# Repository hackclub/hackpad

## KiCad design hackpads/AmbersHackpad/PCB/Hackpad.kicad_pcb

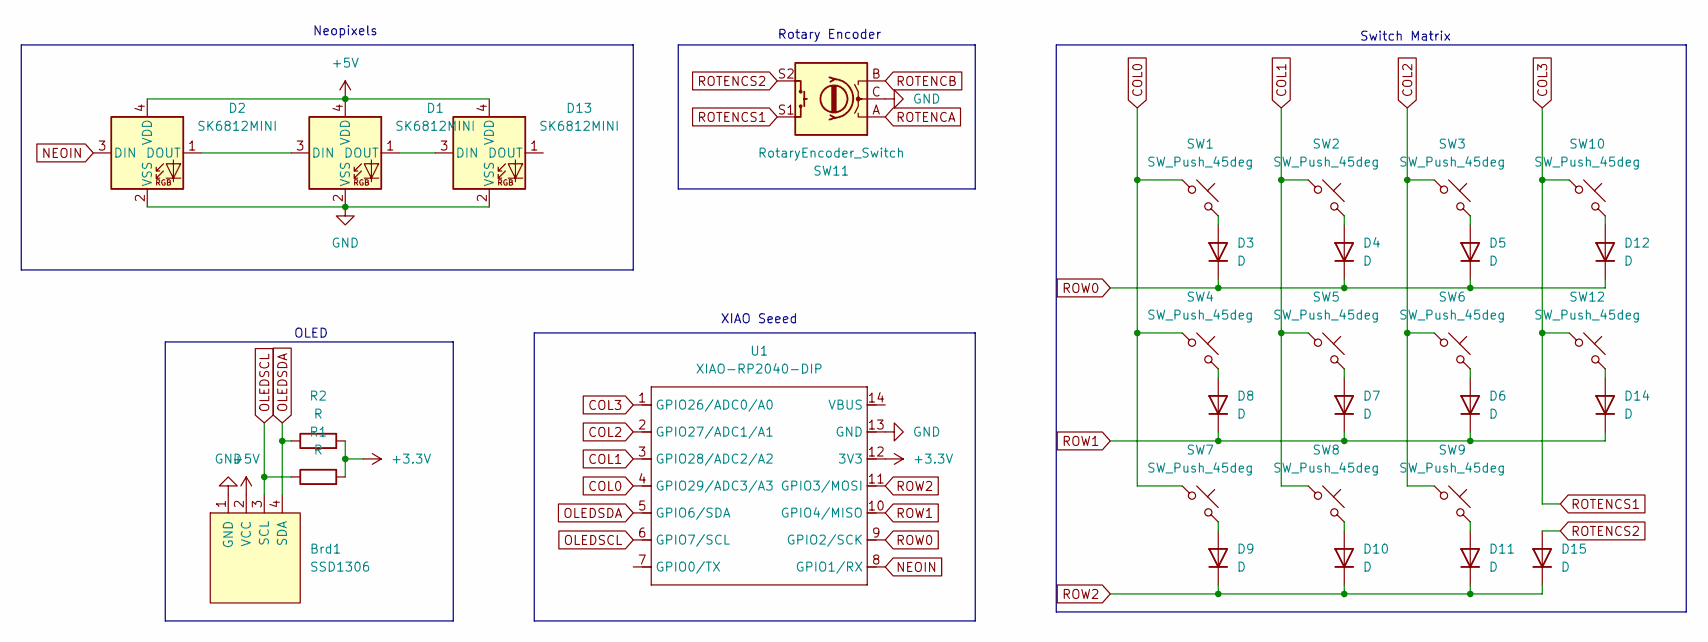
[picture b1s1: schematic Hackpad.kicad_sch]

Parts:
Brd1: SSD1306; 128x64OLED
D1, D2, D13: SK6812MINI; LED_SK6812MINI_PLCC4_3.5x3.5mm_P1.75mm_3D
D3, D4, D5, D6, D7, D8, D9, D10, D11, D12, D14, D15: D; D_DO-35_SOD27_P7.62mm_Horizontal
R1, R2: R; R_Axial_DIN0204_L3.6mm_D1.6mm_P7.62mm_Horizontal
SW1, SW2, SW3, SW4, SW5, SW6, SW7, SW8, SW9, SW10, SW12: SW_Push_45deg; SW_Cherry_MX_1.00u_PCB_3D
SW11: RotaryEncoder_Switch; RotaryEncoder_Alps_EC11E-Switch_Vertical_H20mm_CircularMoun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
U1: XIAO-RP2040-DIP; XIAO-RP2040-DIP-3D

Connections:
+3.3V: R1.2, R2.2, U1.12 (3V3)
+5V: Brd1.2 (VCC), D1.4 (VDD), D2.4 (VDD), D13.4 (VDD)
COL0: SW1.1, SW4.1, SW7.1, U1.4 (GPIO29/ADC3/A3)
COL1: SW2.1, SW5.1, SW8.1, U1.3 (GPIO28/ADC2/A2)
COL2: SW3.1, SW6.1, SW9.1, U1.2 (GPIO27/ADC1/A1)
COL3: SW10.1, SW11.S1, SW12.1, U1.1 (GPIO26/ADC0/A0)
GND: Brd1.1 (GND), D1.2 (VSS), D2.2 (VSS), D13.2 (VSS), SW11.C, U1.13 (GND)
NEOIN: D2.3 (DIN), U1.8 (GPIO1/RX)
unnamed: D1.3 (DIN), D2.1 (DOUT)
unnamed: D1.1 (DOUT), D13.3 (DIN)
unnamed: D3.2 (A), SW1.2
unnamed: D4.2 (A), SW2.2
unnamed: D5.2 (A), SW3.2
unnamed: D6.2 (A), SW6.2
unnamed: D7.2 (A), SW5.2
unnamed: D8.2 (A), SW4.2
unnamed: D9.2 (A), SW7.2
unnamed: D10.2 (A), SW8.2
unnamed: D11.2 (A), SW9.2
unnamed: D12.2 (A), SW10.2
unnamed: D14.2 (A), SW12.2
OLEDSCL: Brd1.3 (SCL), R1.1, U1.6 (GPIO7/SCL)
OLEDSDA: Brd1.4 (SDA), R2.1, U1.5 (GPIO6/SDA)
ROTENCA: SW11.A
ROTENCB: SW11.B
ROTENCS2: D15.2 (A), SW11.S2
ROW0: D3.1 (K), D4.1 (K), D5.1 (K), D12.1 (K), U1.9 (GPIO2/SCK)
ROW1: D6.1 (K), D7.1 (K), D8.1 (K), D14.1 (K), U1.10 (GPIO4/MISO)
ROW2: D9.1 (K), D10.1 (K), D11.1 (K), D15.1 (K), U1.11 (GPIO3/MOSI)

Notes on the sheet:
XIAO Seeed
Neopixels
Rotary Encoder
OLED
Switch Matrix

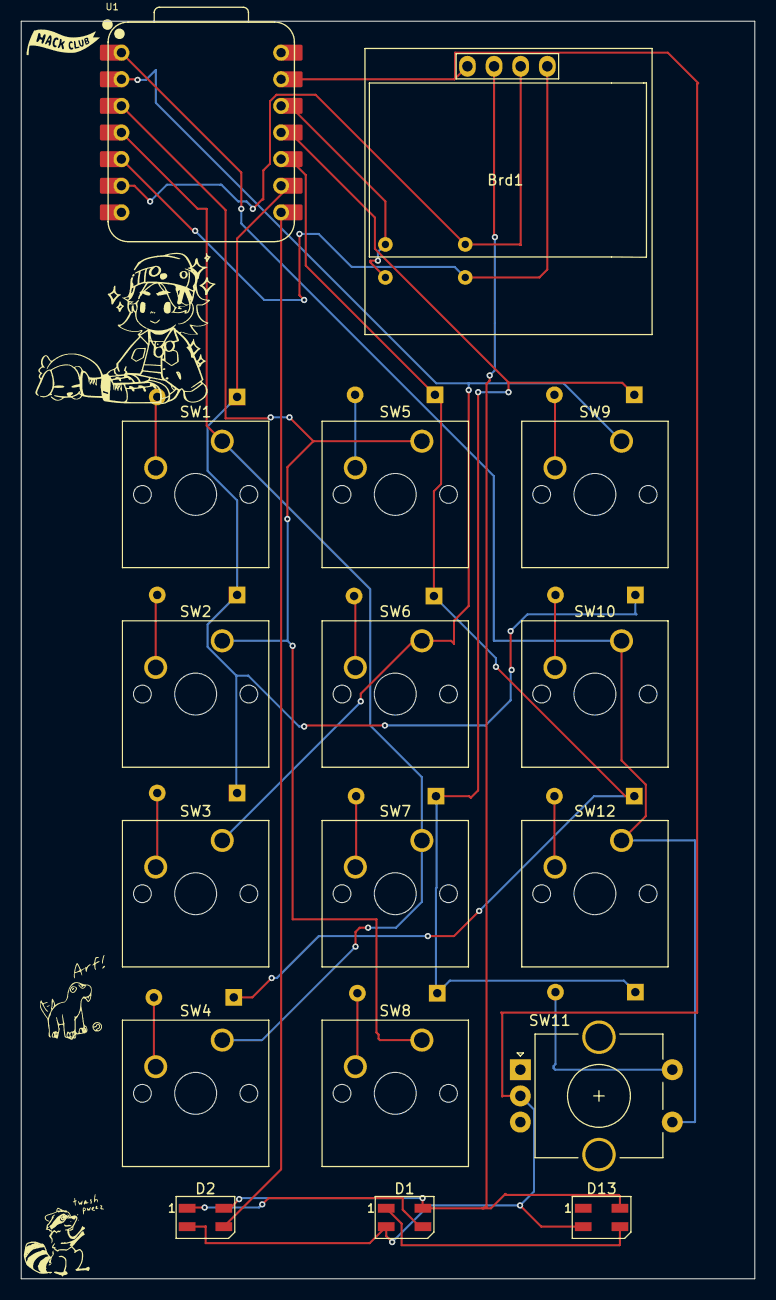
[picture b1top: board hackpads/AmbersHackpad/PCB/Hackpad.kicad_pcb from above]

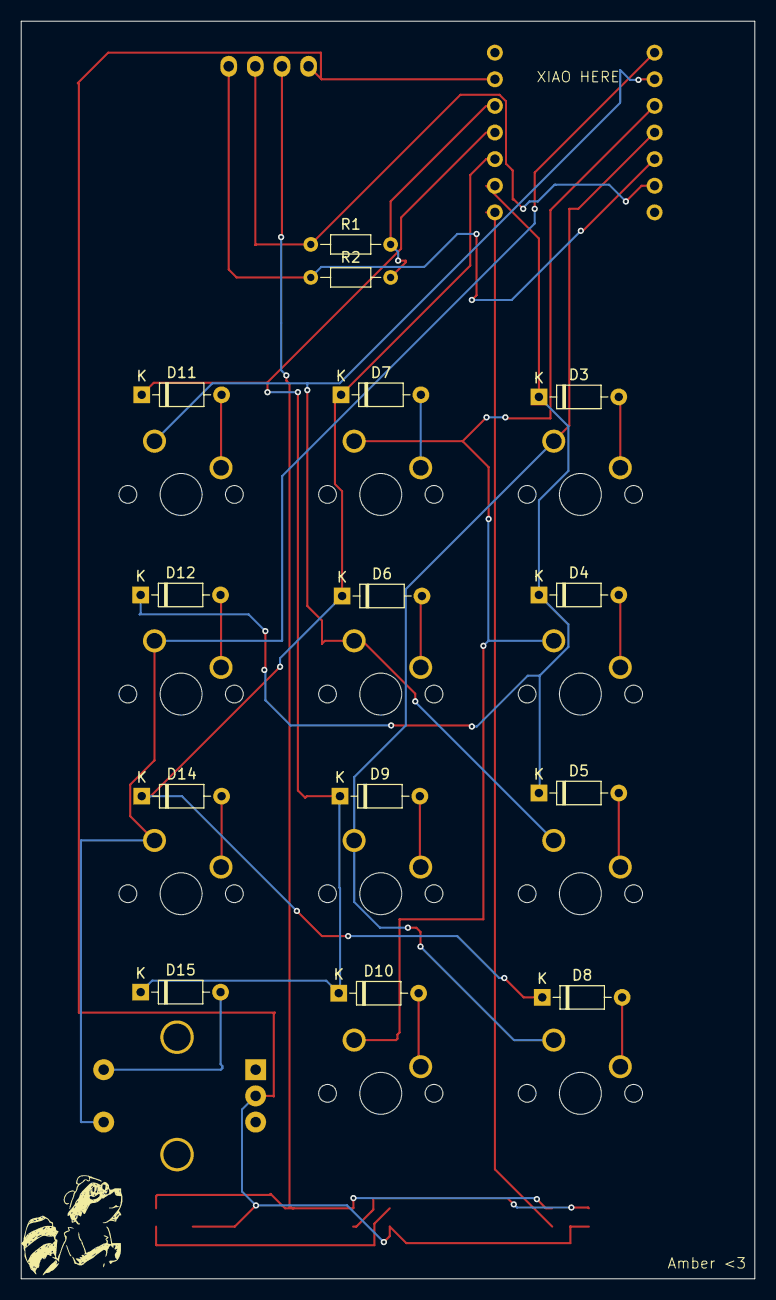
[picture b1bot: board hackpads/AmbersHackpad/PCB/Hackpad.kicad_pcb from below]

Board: 2 copper layers, 70.0 x 120.0 mm, 31 parts (14 on the bottom side), 27 nets.

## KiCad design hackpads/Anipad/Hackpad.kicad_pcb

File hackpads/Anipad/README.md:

# The Anipad

## Overview

Hey! This is Anicetus, and here is my Hackpad, a macropad project from https://hackclub.com. It uses a Seeed Studio XIAO RP2040 with a custom-made case, PCB, and QMK firmware.
It has 11 buttons (not including the rotary encoder) aligned in a 4x3 matrix. The Anipad's primary use is to control my 3D printer without access to a phone or computer. It'll plug into my Raspberry Pi which controls the printer and send commands to print files, move the axes, etc.
The Anipad is equipped with a 0.91" OLED screen and a rotary encoder.

## About the Anipad

I can shamelessly say that I copied @grimsteel a lot on Slack. He was a big help to getting this thing rolling. However, most of the PCB and all of the case is my own design. On the back of the case is a Penrose Triangle, commonly known as the Impossible Triangle. I have a semi-obssession with it, and it only seemed right to include it.
The name "Anipad" comes from my name, Anicetus, which means "Unconquerable" in Latin, a language I'm proud to say I can speak ~~decently well~~ OK I guess. Autem, sum non bonus in conspectu populi.
<br/>***ANYWAYS***, I love coding, making, and hacking, and despite arriving with less than 10 days left in the Hackpad project, I feel I did decently well. And, of course, I needed to add its name in the front.
<br/>

<br/>
<br/>
~ Anicetus
<br/>
<sub>Holy cow was designing the case hard<sub>

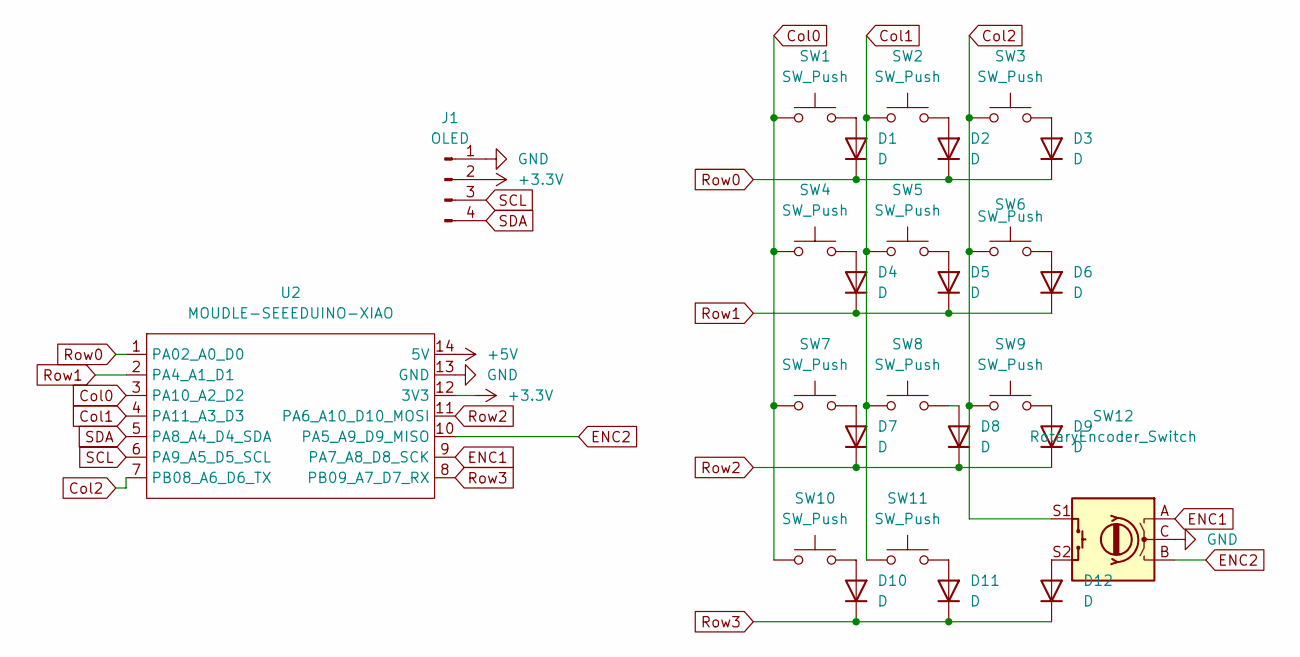
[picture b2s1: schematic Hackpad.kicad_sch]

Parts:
D1, D2, D3, D4, D5, D6, D7, D8, D9, D10, D11, D12: D; D_DO-35_SOD27_P7.62mm_Horizontal
J1: OLED; SSD1306-0.91-OLED-4pin-128x32
SW1, SW2, SW3, SW4, SW5, SW6, SW7, SW8, SW9, SW10, SW11: SW_Push; SW_Cherry_MX_1.00u_PCB
SW12: RotaryEncoder_Switch; RotaryEncoder_Alps_EC11E-Switch_Vertical_H20mm
U2: MOUDLE-SEEEDUINO-XIAO; XIAO-Generic-Thruhole-14P-2.54-21X17.8MM

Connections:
+3.3V: J1.2, U2.12 (3V3)
+5V: U2.14 (5V)
Col0: SW1.1, SW4.1, SW7.1, SW10.1, U2.3 (PA10_A2_D2)
Col1: SW2.1, SW5.1, SW8.1, SW11.1, U2.4 (PA11_A3_D3)
Col2: SW3.1, SW6.1, SW9.1, SW12.S1, U2.7 (PB08_A6_D6_TX)
ENC1: SW12.A, U2.9 (PA7_A8_D8_SCK)
ENC2: SW12.B, U2.10 (PA5_A9_D9_MISO)
GND: J1.1, SW12.C, U2.13 (GND)
unnamed: D1.2 (A), SW1.2
unnamed: D2.2 (A), SW2.2
unnamed: D3.2 (A), SW3.2
unnamed: D4.2 (A), SW4.2
unnamed: D5.2 (A), SW5.2
unnamed: D6.2 (A), SW6.2
unnamed: D7.2 (A), SW7.2
unnamed: D8.2 (A), SW8.2
unnamed: D9.2 (A), SW9.2
unnamed: D10.2 (A), SW10.2
unnamed: D11.2 (A), SW11.2
unnamed: D12.2 (A), SW12.S2
Row0: D1.1 (K), D2.1 (K), D3.1 (K), U2.1 (PA02_A0_D0)
Row1: D4.1 (K), D5.1 (K), D6.1 (K), U2.2 (PA4_A1_D1)
Row2: D7.1 (K), D8.1 (K), D9.1 (K), U2.11 (PA6_A10_D10_MOSI)
Row3: D10.1 (K), D11.1 (K), D12.1 (K), U2.8 (PB09_A7_D7_RX)
SCL: J1.3, U2.6 (PA9_A5_D5_SCL)
SDA: J1.4, U2.5 (PA8_A4_D4_SDA)

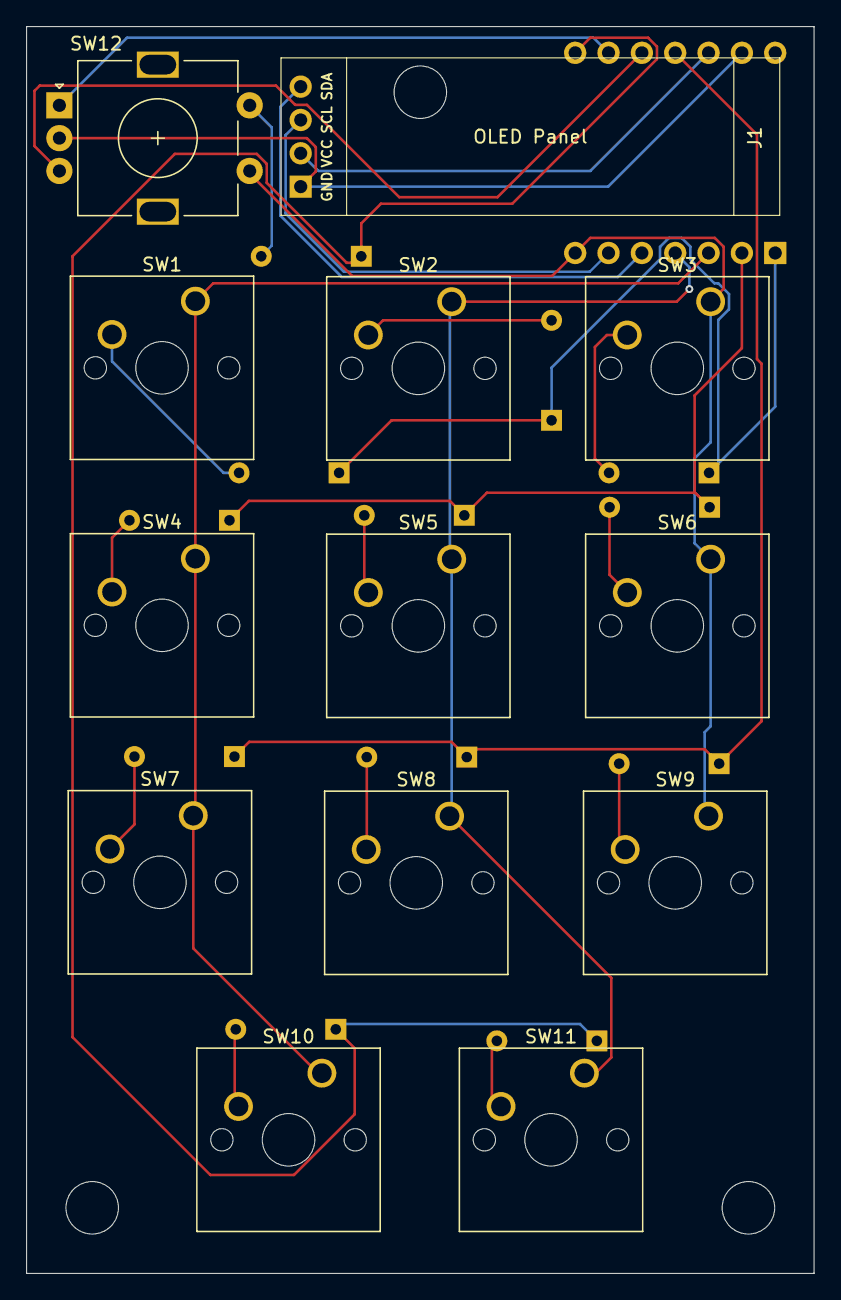
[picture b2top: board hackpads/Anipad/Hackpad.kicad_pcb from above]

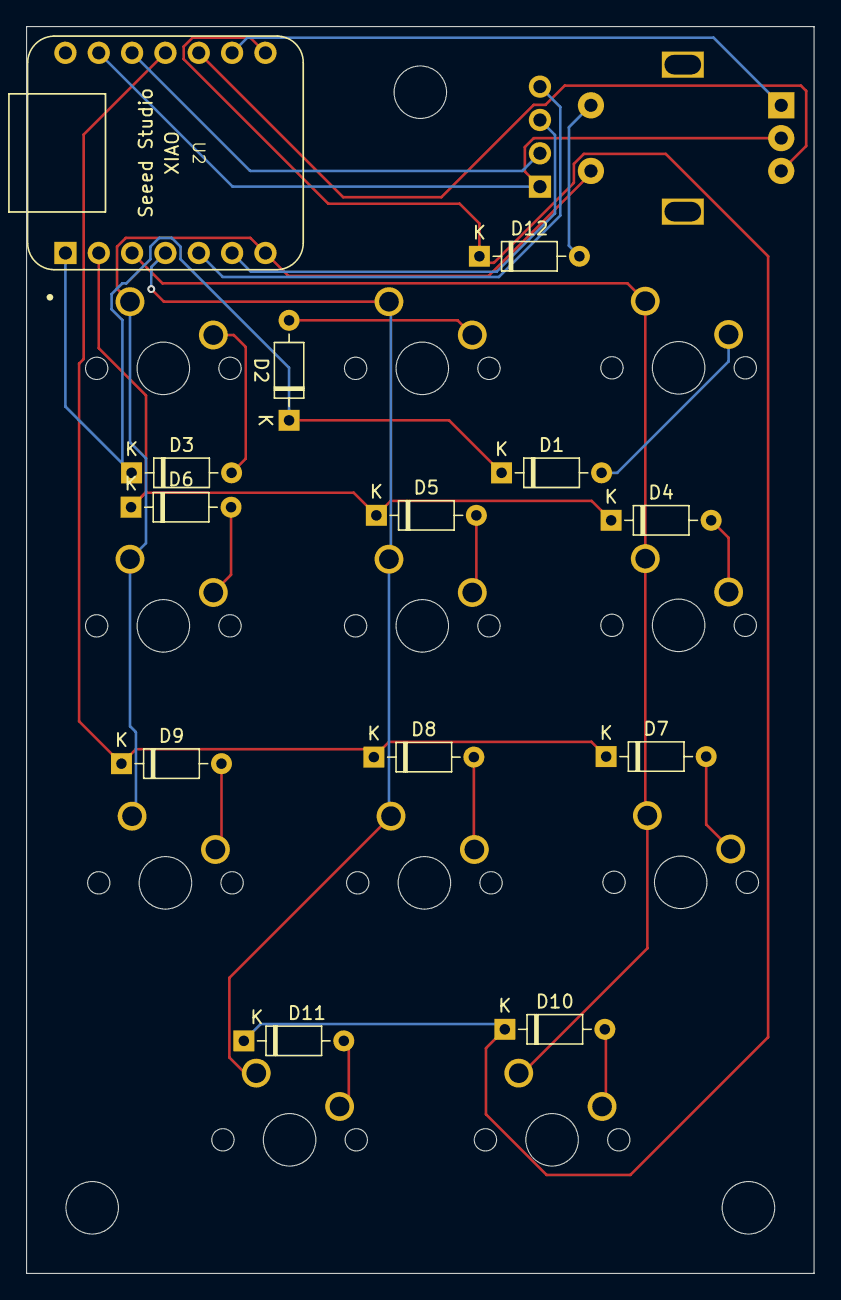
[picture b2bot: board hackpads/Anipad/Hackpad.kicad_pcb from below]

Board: 2 copper layers, 60.0 x 95.0 mm, 26 parts (13 on the bottom side), 25 nets.

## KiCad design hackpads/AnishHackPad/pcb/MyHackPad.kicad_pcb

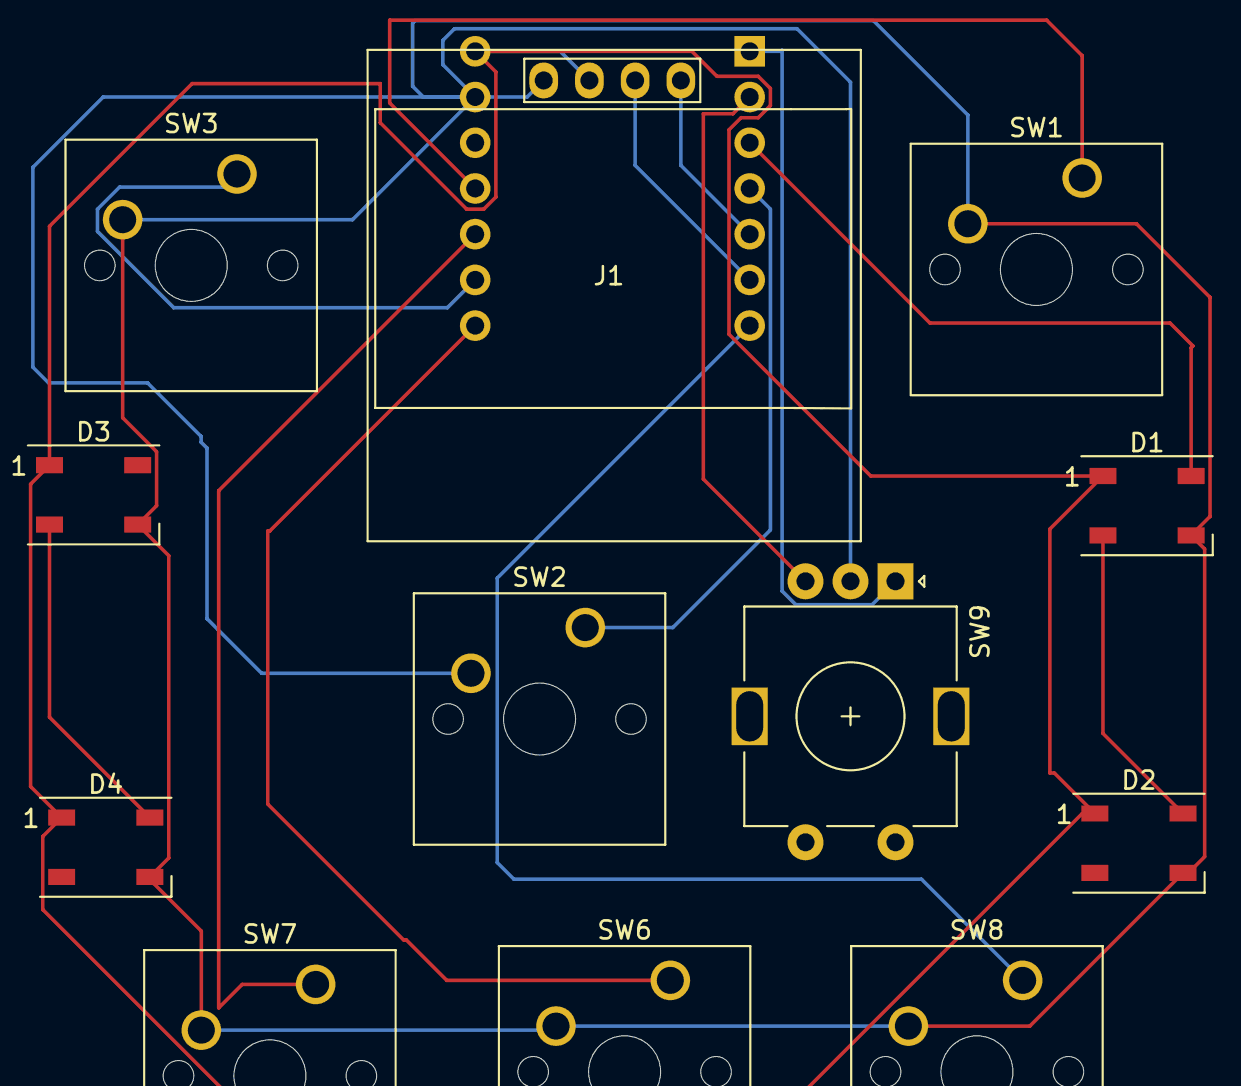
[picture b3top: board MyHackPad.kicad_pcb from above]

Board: 2 copper layers, 13 parts (1 on the bottom side), 16 nets.

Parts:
D1, D2, D3, D4: WS2812B; LED_WS2812B_PLCC4_5.0x5.0mm_P3.2mm
J1: OLED-128x64; 128x64OLED
SW1, SW2, SW3, SW6, SW7, SW8: SW_Push; SW_Cherry_MX_1.00u_PCB
SW9: RotaryEncoder; RotaryEncoder_Alps_EC11E-Switch_Vertical_H20mm
U1: Seeed Studio XIAO SAMD21; XIAO-Generic-Thruhole-14P-2.54-21X17.8MM

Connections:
GND: D1.3 (VSS), D2.3 (VSS), D3.3 (VSS), D4.3 (VSS), J1.1 (GND), SW1.2, SW2.2, SW3.2, SW6.2, SW7.2, SW8.2, SW9.C, U1.13 (GND)
unnamed: D1.4 (DIN), U1.3 (PA10_A2_D2)
unnamed: D1.2 (DOUT), D2.4 (DIN)
unnamed: D1.1 (VDD), D2.1 (VDD), D3.1 (VDD), D4.1 (VDD), J1.2 (VCC), U1.14 (5V)
unnamed: D2.2 (DOUT), D3.4 (DIN)
unnamed: D3.2 (DOUT), D4.4 (DIN)
unnamed: J1.3 (SCL), U1.6 (PA9_A5_D5_SCL)
unnamed: J1.4 (SDA), U1.5 (PA8_A4_D4_SDA)
unnamed: SW9.A, U1.1 (PA02_A0_D0)
unnamed: SW9.B, U1.2 (PA4_A1_D1)
unnamed: SW7.1, U1.10 (PA5_A9_D9_MISO)
unnamed: SW1.1, U1.11 (PA6_A10_D10_MOSI)
unnamed: SW3.1, U1.9 (PA7_A8_D8_SCK)
unnamed: SW2.1, U1.4 (PA11_A3_D3)
unnamed: SW8.1, U1.7 (PB08_A6_D6_TX)
unnamed: SW6.1, U1.8 (PB09_A7_D7_RX)

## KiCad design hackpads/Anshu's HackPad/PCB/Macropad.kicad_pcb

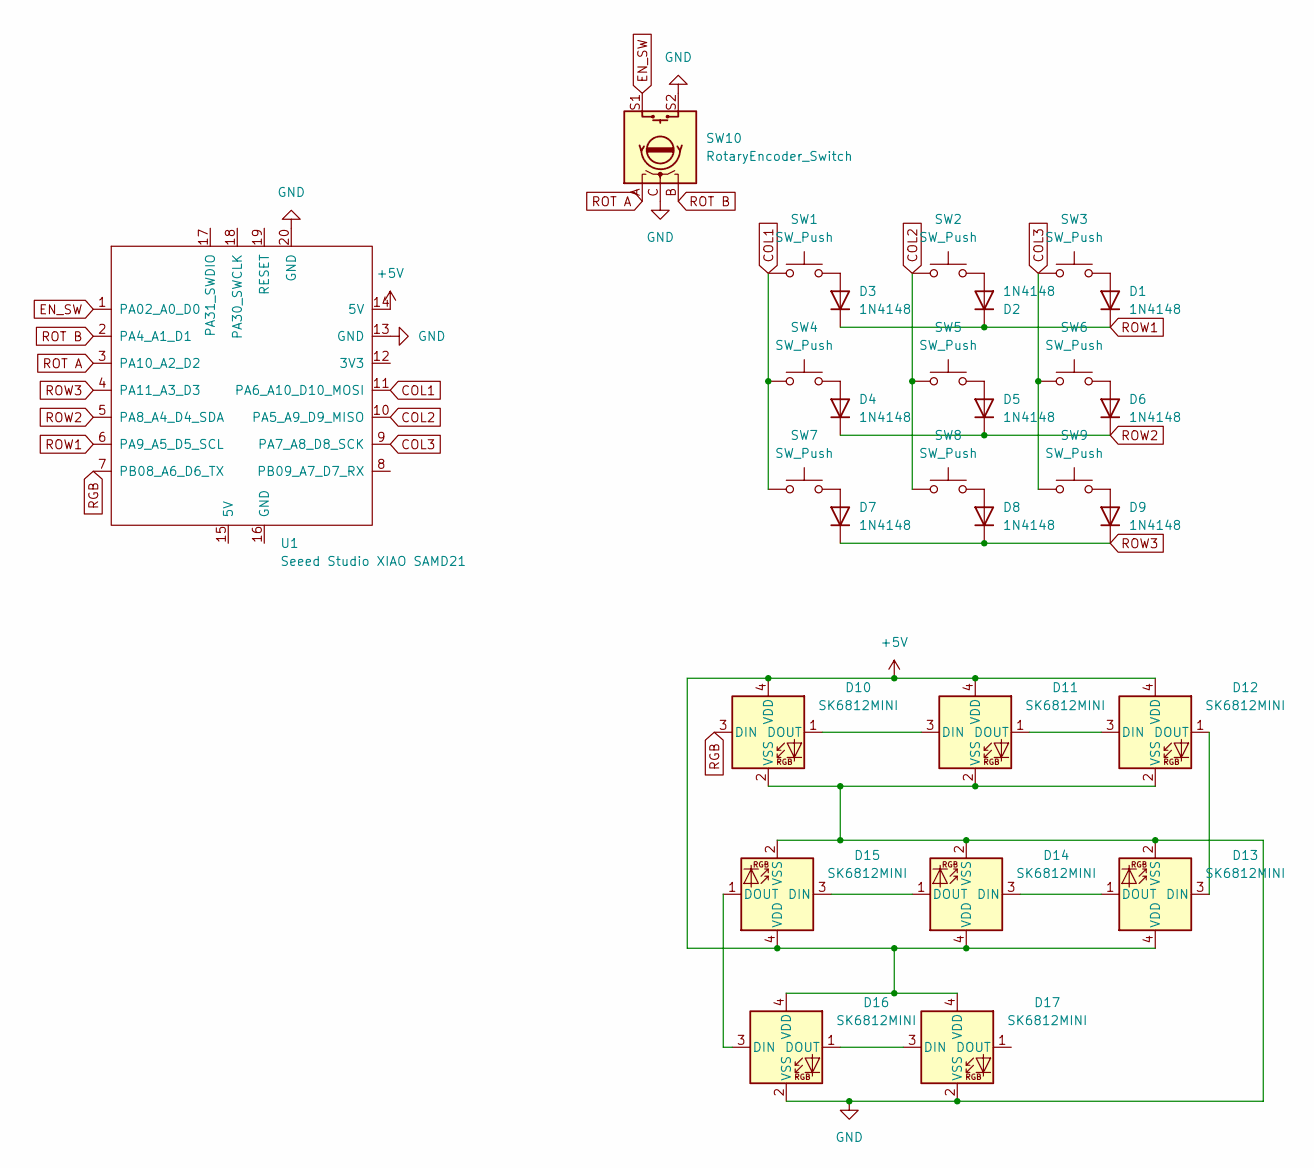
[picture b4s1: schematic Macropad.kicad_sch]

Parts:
D1, D2, D3, D4, D5, D6, D7, D8, D9: 1N4148; D_DO-35_SOD27_P7.62mm_Horizontal
D10, D11, D12, D13, D14, D15, D16, D17: SK6812MINI; LED_SK6812MINI_PLCC4_3.5x3.5mm_P1.75mm
SW1, SW2, SW3, SW4, SW5, SW6, SW7, SW8, SW9: SW_Push; SW_Cherry_MX_1.00u_PCB
SW10: RotaryEncoder_Switch; RotaryEncoder_Alps_EC11E-Switch_Vertical_H20mm_CircularMoun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
U1: Seeed Studio XIAO SAMD21; XIAO-RP2040-DIP

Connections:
+5V: D10.4 (VDD), D11.4 (VDD), D12.4 (VDD), D13.4 (VDD), D14.4 (VDD), D15.4 (VDD), D16.4 (VDD), D17.4 (VDD), U1.14 (5V)
COL1: SW1.1, SW4.1, SW7.1, U1.11 (PA6_A10_D10_MOSI)
COL2: SW2.1, SW5.1, SW8.1, U1.10 (PA5_A9_D9_MISO)
COL3: SW3.1, SW6.1, SW9.1, U1.9 (PA7_A8_D8_SCK)
EN_SW: SW10.S1, U1.1 (PA02_A0_D0)
GND: D10.2 (VSS), D11.2 (VSS), D12.2 (VSS), D13.2 (VSS), D14.2 (VSS), D15.2 (VSS), D16.2 (VSS), D17.2 (VSS), SW10.C, SW10.S2, U1.13 (GND), U1.20 (GND)
unnamed: D1.2 (A), SW3.2
unnamed: D2.2 (A), SW2.2
unnamed: D3.2 (A), SW1.2
unnamed: D4.2 (A), SW4.2
unnamed: D5.2 (A), SW5.2
unnamed: D6.2 (A), SW6.2
unnamed: D7.2 (A), SW7.2
unnamed: D8.2 (A), SW8.2
unnamed: D9.2 (A), SW9.2
unnamed: D10.1 (DOUT), D11.3 (DIN)
unnamed: D11.1 (DOUT), D12.3 (DIN)
unnamed: D12.1 (DOUT), D13.3 (DIN)
unnamed: D13.1 (DOUT), D14.3 (DIN)
unnamed: D14.1 (DOUT), D15.3 (DIN)
unnamed: D15.1 (DOUT), D16.3 (DIN)
unnamed: D16.1 (DOUT), D17.3 (DIN)
RGB: D10.3 (DIN), U1.7 (PB08_A6_D6_TX)
ROT A: SW10.A, U1.3 (PA10_A2_D2)
ROT B: SW10.B, U1.2 (PA4_A1_D1)
ROW1: D1.1 (K), D2.1 (K), D3.1 (K), U1.6 (PA9_A5_D5_SCL)
ROW2: D4.1 (K), D5.1 (K), D6.1 (K), U1.5 (PA8_A4_D4_SDA)
ROW3: D7.1 (K), D8.1 (K), D9.1 (K), U1.4 (PA11_A3_D3)

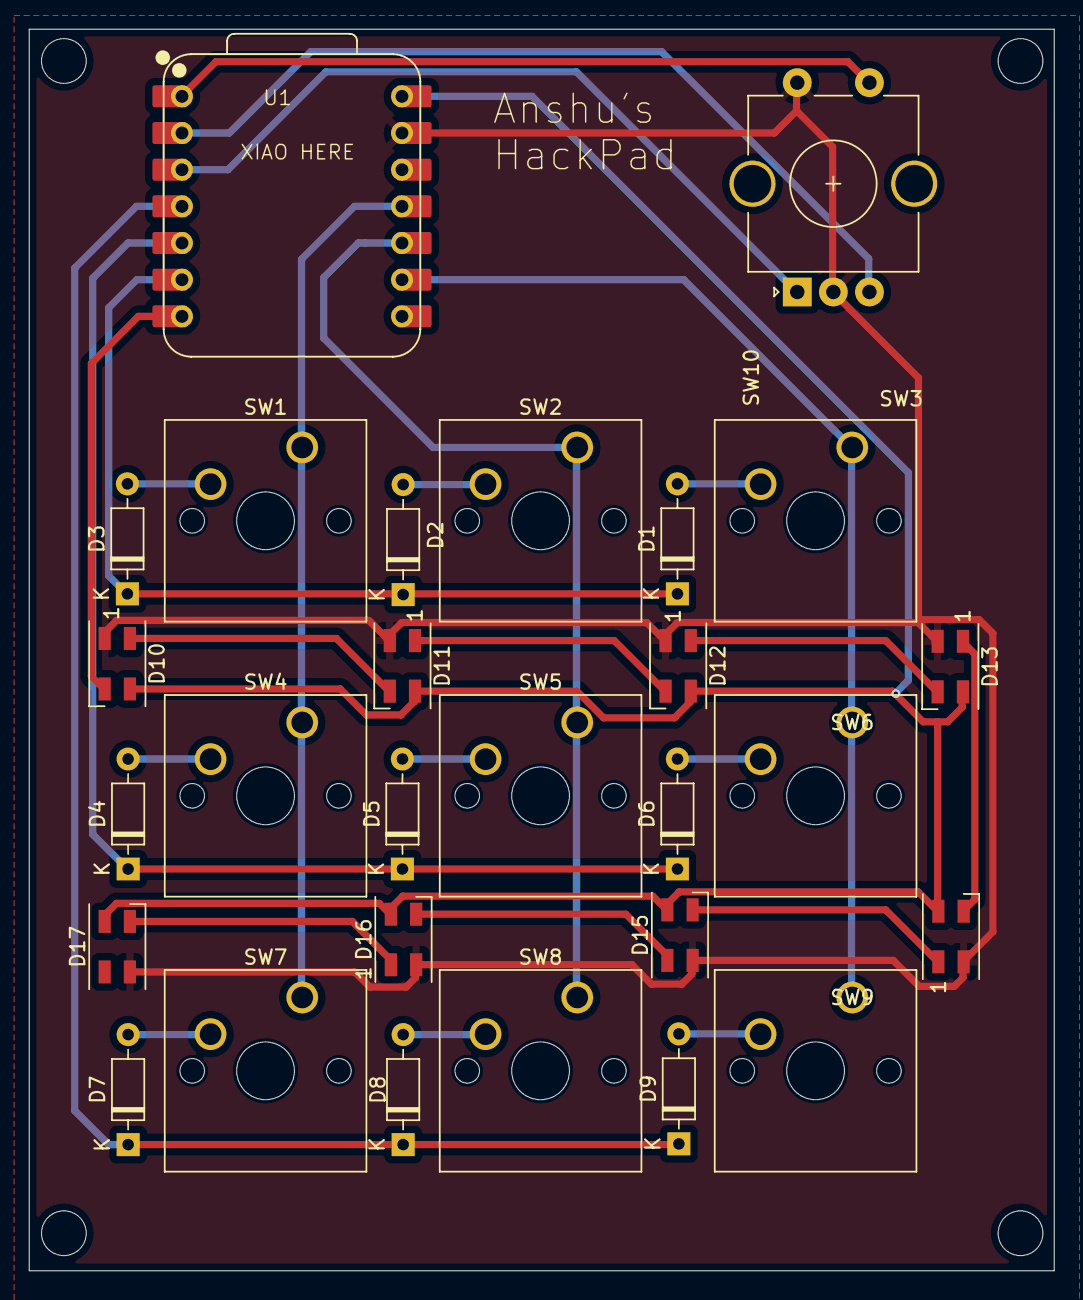
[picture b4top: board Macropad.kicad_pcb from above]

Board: 2 copper layers, 71.0 x 86.0 mm, 28 parts (0 on the bottom side), 28 nets.

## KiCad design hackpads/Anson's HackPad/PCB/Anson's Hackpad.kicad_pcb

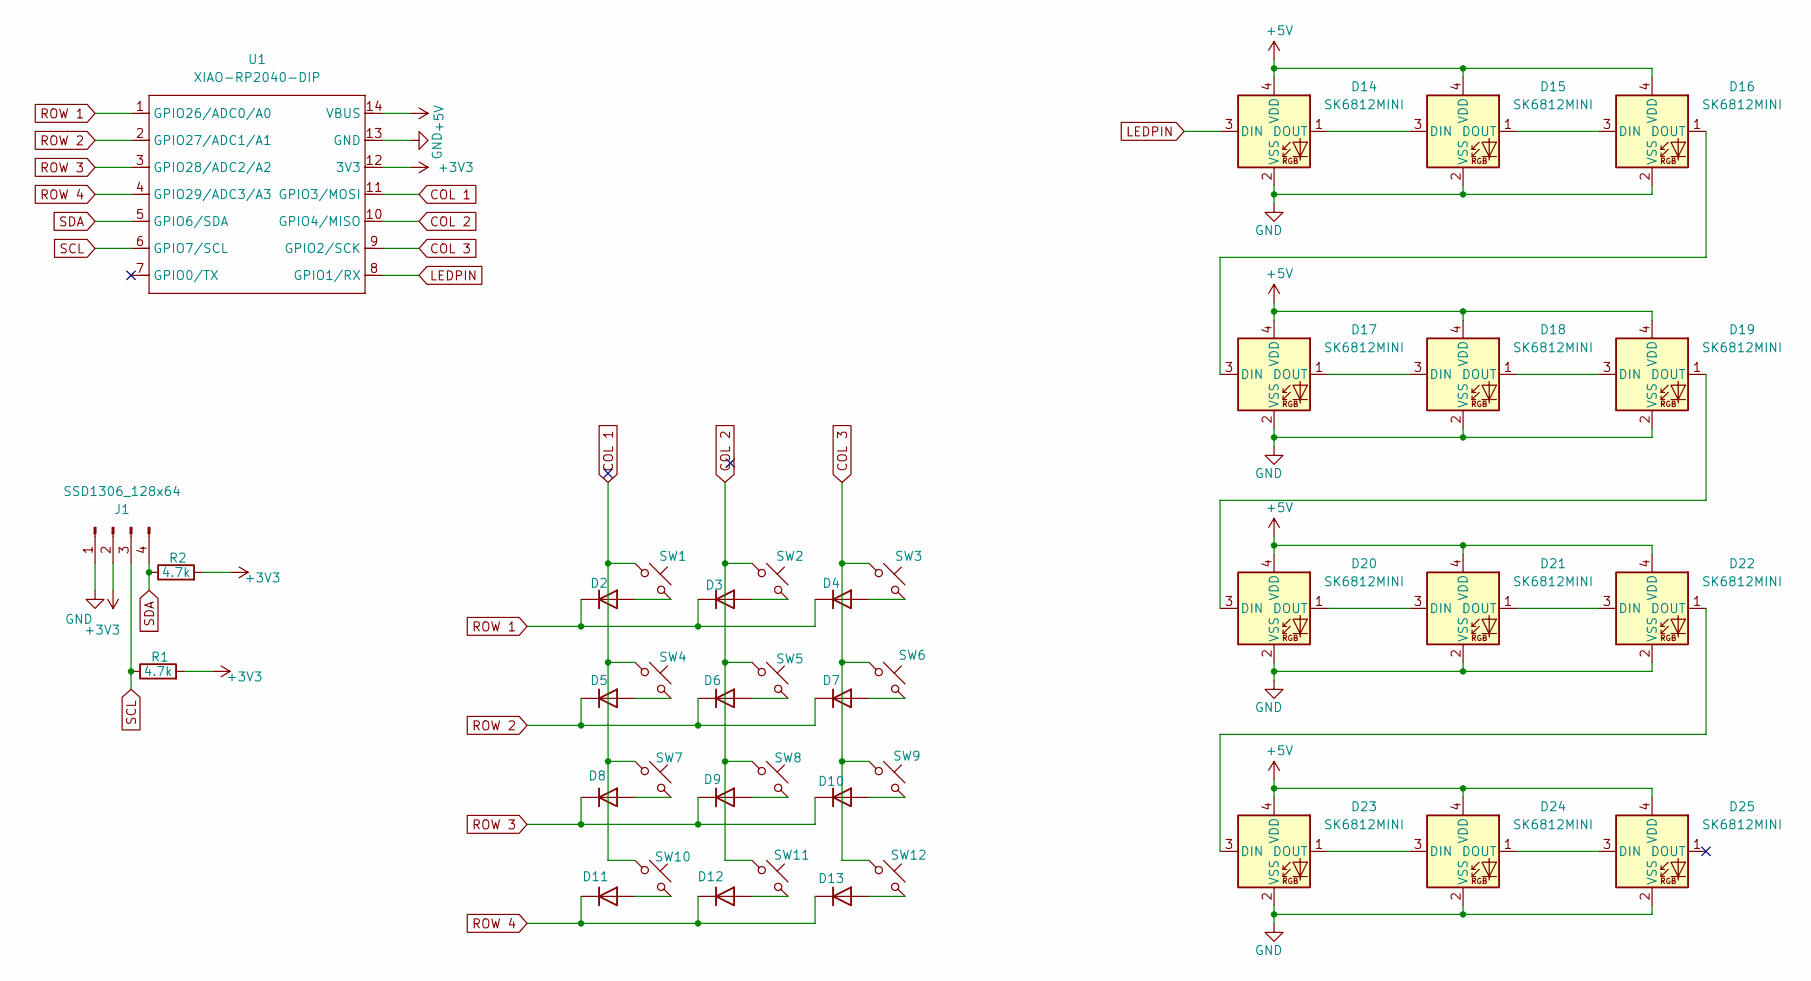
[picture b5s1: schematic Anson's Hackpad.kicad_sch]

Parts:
D2, D3, D4, D5, D6, D7, D8, D9, D10, D11, D12, D13: 1N4148; D_DO-35_SOD27_P7.62mm_Horizontal
D14, D15, D16, D17, D18, D19, D20, D21, D22, D23, D24, D25: SK6812MINI; SK6812MINI-E
J1: SSD1306_128x64; SSD1306-0.91-OLED-4pin-128x32
R1, R2: 4.7k; R_Axial_DIN0204_L3.6mm_D1.6mm_P7.62mm_Horizontal
SW1, SW2, SW3, SW4, SW5, SW6, SW7, SW8, SW9, SW10, SW11, SW12: SW_Push_45deg; AnsonSwitchWithKeyCapsCherry
U1: XIAO-RP2040-DIP; XIAO-RP2040-SMD

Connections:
+3V3: J1.2, R1.2, R2.2, U1.12 (3V3)
+5V: D14.4 (VDD), D15.4 (VDD), D16.4 (VDD), D17.4 (VDD), D18.4 (VDD), D19.4 (VDD), D20.4 (VDD), D21.4 (VDD), D22.4 (VDD), D23.4 (VDD), D24.4 (VDD), D25.4 (VDD), U1.14 (VBUS)
COL 1: SW1.1, SW4.1, SW7.1, SW10.1, U1.11 (GPIO3/MOSI)
COL 2: SW2.1, SW5.1, SW8.1, SW11.1, U1.10 (GPIO4/MISO)
COL 3: SW3.1, SW6.1, SW9.1, SW12.1, U1.9 (GPIO2/SCK)
GND: D14.2 (VSS), D15.2 (VSS), D16.2 (VSS), D17.2 (VSS), D18.2 (VSS), D19.2 (VSS), D20.2 (VSS), D21.2 (VSS), D22.2 (VSS), D23.2 (VSS), D24.2 (VSS), D25.2 (VSS), J1.1, U1.13 (GND)
LEDPIN: D14.3 (DIN), U1.8 (GPIO1/RX)
unnamed: D2.2 (A), SW1.2
unnamed: D3.2 (A), SW2.2
unnamed: D4.2 (A), SW3.2
unnamed: D5.2 (A), SW4.2
unnamed: D6.2 (A), SW5.2
unnamed: D7.2 (A), SW6.2
unnamed: D8.2 (A), SW7.2
unnamed: D9.2 (A), SW8.2
unnamed: D10.2 (A), SW9.2
unnamed: D11.2 (A), SW10.2
unnamed: D12.2 (A), SW11.2
unnamed: D13.2 (A), SW12.2
unnamed: D14.1 (DOUT), D15.3 (DIN)
unnamed: D15.1 (DOUT), D16.3 (DIN)
unnamed: D16.1 (DOUT), D17.3 (DIN)
unnamed: D17.1 (DOUT), D18.3 (DIN)
unnamed: D18.1 (DOUT), D19.3 (DIN)
unnamed: D19.1 (DOUT), D20.3 (DIN)
unnamed: D20.1 (DOUT), D21.3 (DIN)
unnamed: D21.1 (DOUT), D22.3 (DIN)
unnamed: D22.1 (DOUT), D23.3 (DIN)
unnamed: D23.1 (DOUT), D24.3 (DIN)
unnamed: D24.1 (DOUT), D25.3 (DIN)
ROW 1: D2.1 (K), D3.1 (K), D4.1 (K), U1.1 (GPIO26/ADC0/A0)
ROW 2: D5.1 (K), D6.1 (K), D7.1 (K), U1.2 (GPIO27/ADC1/A1)
ROW 3: D8.1 (K), D9.1 (K), D10.1 (K), U1.3 (GPIO28/ADC2/A2)
ROW 4: D11.1 (K), D12.1 (K), D13.1 (K), U1.4 (GPIO29/ADC3/A3)
SCL: J1.3, R1.1, U1.6 (GPIO7/SCL)
SDA: J1.4, R2.1, U1.5 (GPIO6/SDA)

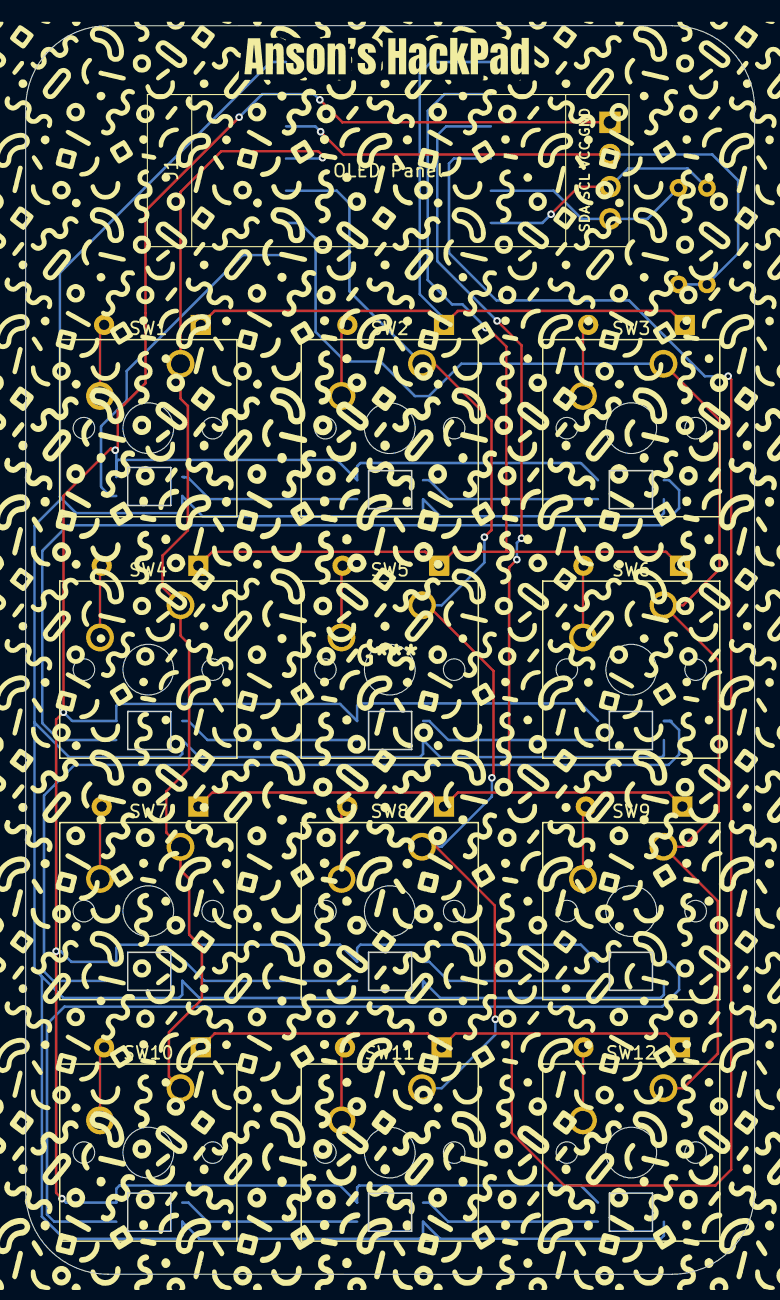
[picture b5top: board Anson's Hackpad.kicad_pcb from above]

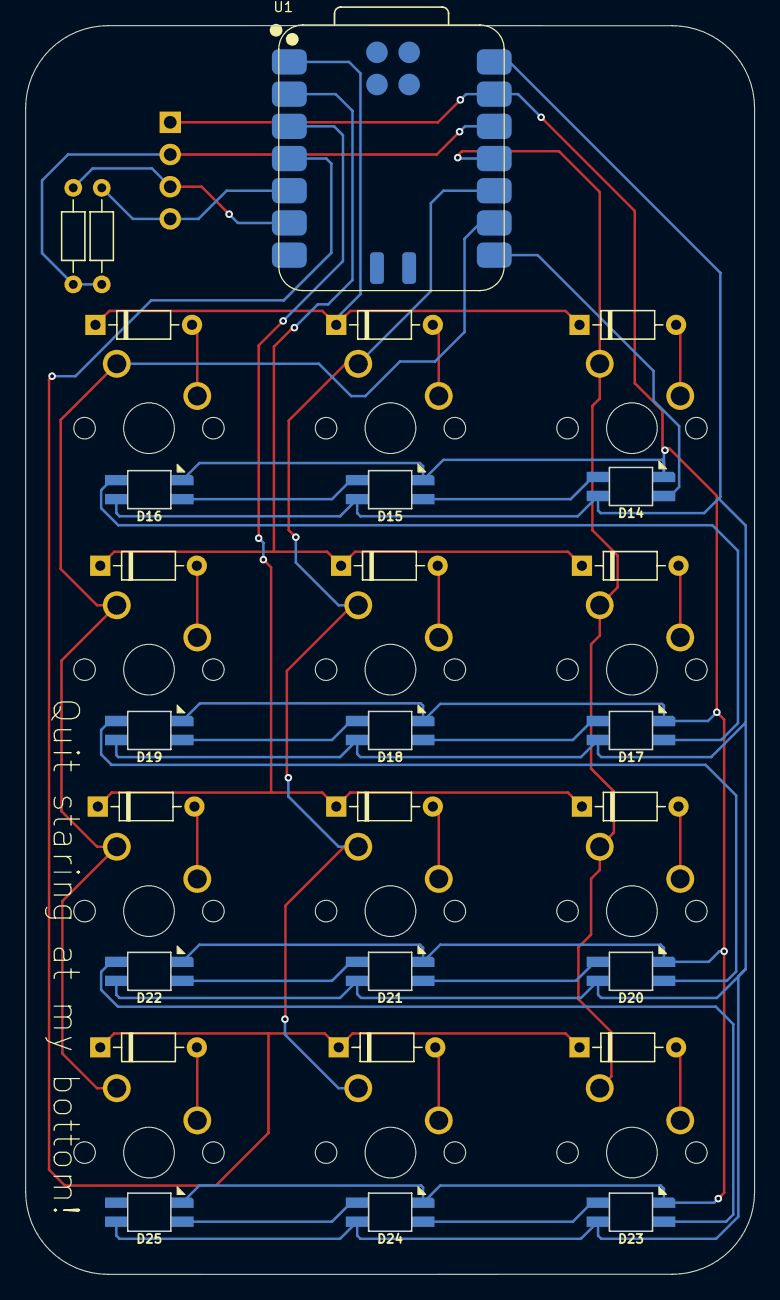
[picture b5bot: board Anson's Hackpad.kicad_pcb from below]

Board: 2 copper layers, 57.5 x 98.5 mm, 40 parts (27 on the bottom side), 36 nets.

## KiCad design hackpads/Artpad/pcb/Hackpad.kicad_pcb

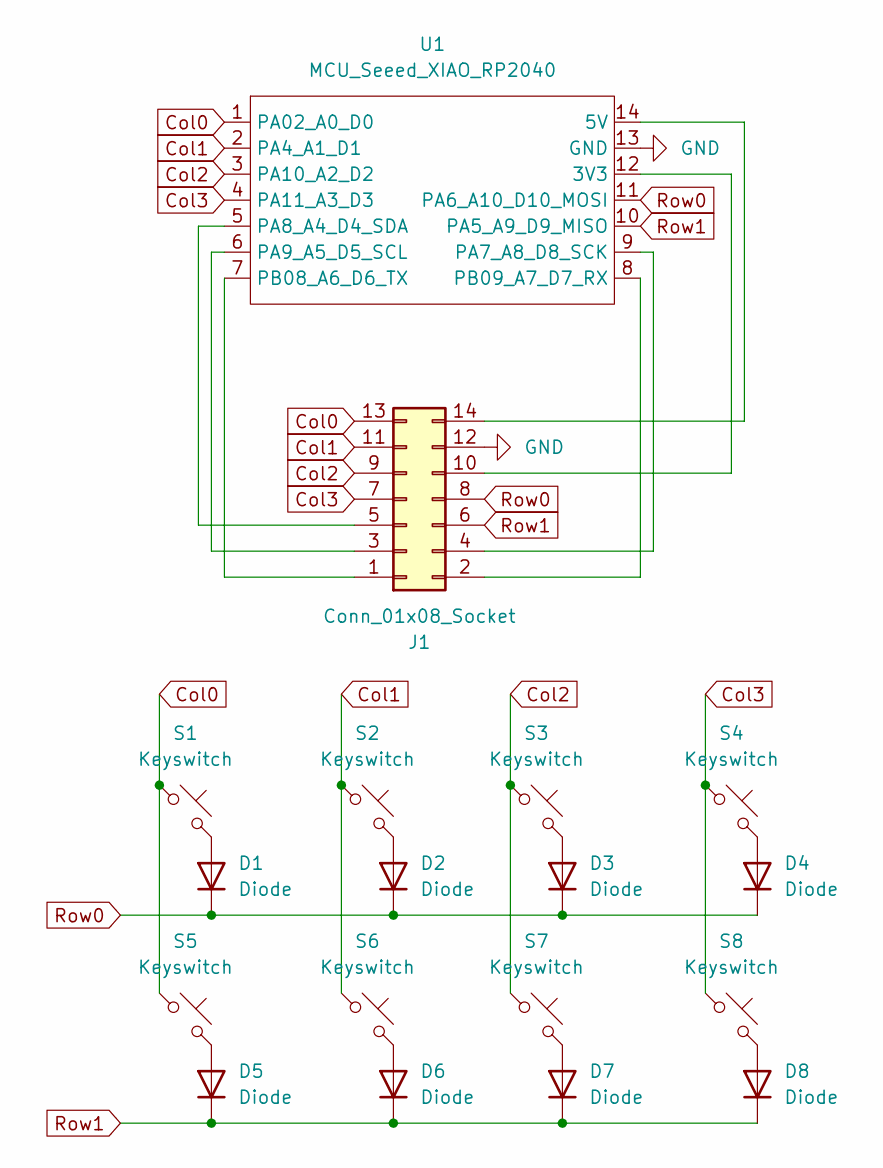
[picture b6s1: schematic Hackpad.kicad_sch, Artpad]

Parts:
D1, D2, D3, D4, D5, D6, D7, D8: Diode; Diode_DO-35
J1: Conn_01x08_Socket; PinSocket_2x07_P2.54mm_Horizontal
S1, S2, S3, S4, S5, S6, S7, S8: Keyswitch; Hotswap_MX_1.00u
U1: MCU_Seeed_XIAO_RP2040; Seeed_XIAO_RP2040

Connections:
Col0: J1.13, S1.1, S5.1, U1.1 (PA02_A0_D0)
Col1: J1.11, S2.1, S6.1, U1.2 (PA4_A1_D1)
Col2: J1.9, S3.1, S7.1, U1.3 (PA10_A2_D2)
Col3: J1.7, S4.1, S8.1, U1.4 (PA11_A3_D3)
GND: J1.12, U1.13 (GND)
unnamed: D1.2 (A), S1.2
unnamed: D2.2 (A), S2.2
unnamed: D3.2 (A), S3.2
unnamed: D4.2 (A), S4.2
unnamed: D5.2 (A), S5.2
unnamed: D6.2 (A), S6.2
unnamed: D7.2 (A), S7.2
unnamed: D8.2 (A), S8.2
unnamed: J1.1, U1.7 (PB08_A6_D6_TX)
unnamed: J1.2, U1.8 (PB09_A7_D7_RX)
unnamed: J1.3, U1.6 (PA9_A5_D5_SCL)
unnamed: J1.4, U1.9 (PA7_A8_D8_SCK)
unnamed: J1.5, U1.5 (PA8_A4_D4_SDA)
unnamed: J1.10, U1.12 (3V3)
unnamed: J1.14, U1.14 (5V)
Row0: D1.1 (K), D2.1 (K), D3.1 (K), D4.1 (K), J1.8, U1.11 (PA6_A10_D10_MOSI)
Row1: D5.1 (K), D6.1 (K), D7.1 (K), D8.1 (K), J1.6, U1.10 (PA5_A9_D9_MISO)

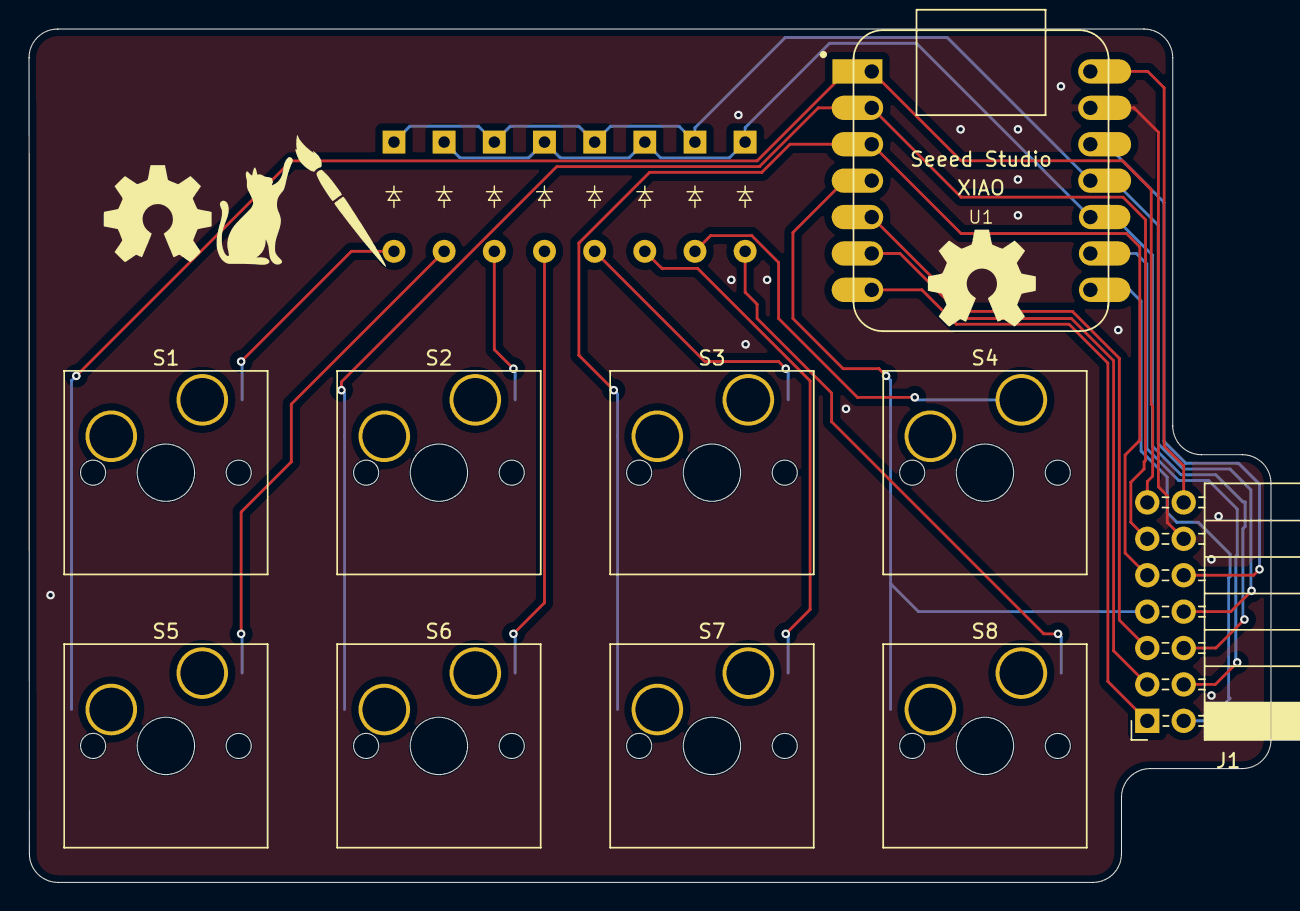
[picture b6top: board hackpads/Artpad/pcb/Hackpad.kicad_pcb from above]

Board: 2 copper layers, 86.7 x 59.5 mm, 18 parts (0 on the bottom side), 22 nets.
